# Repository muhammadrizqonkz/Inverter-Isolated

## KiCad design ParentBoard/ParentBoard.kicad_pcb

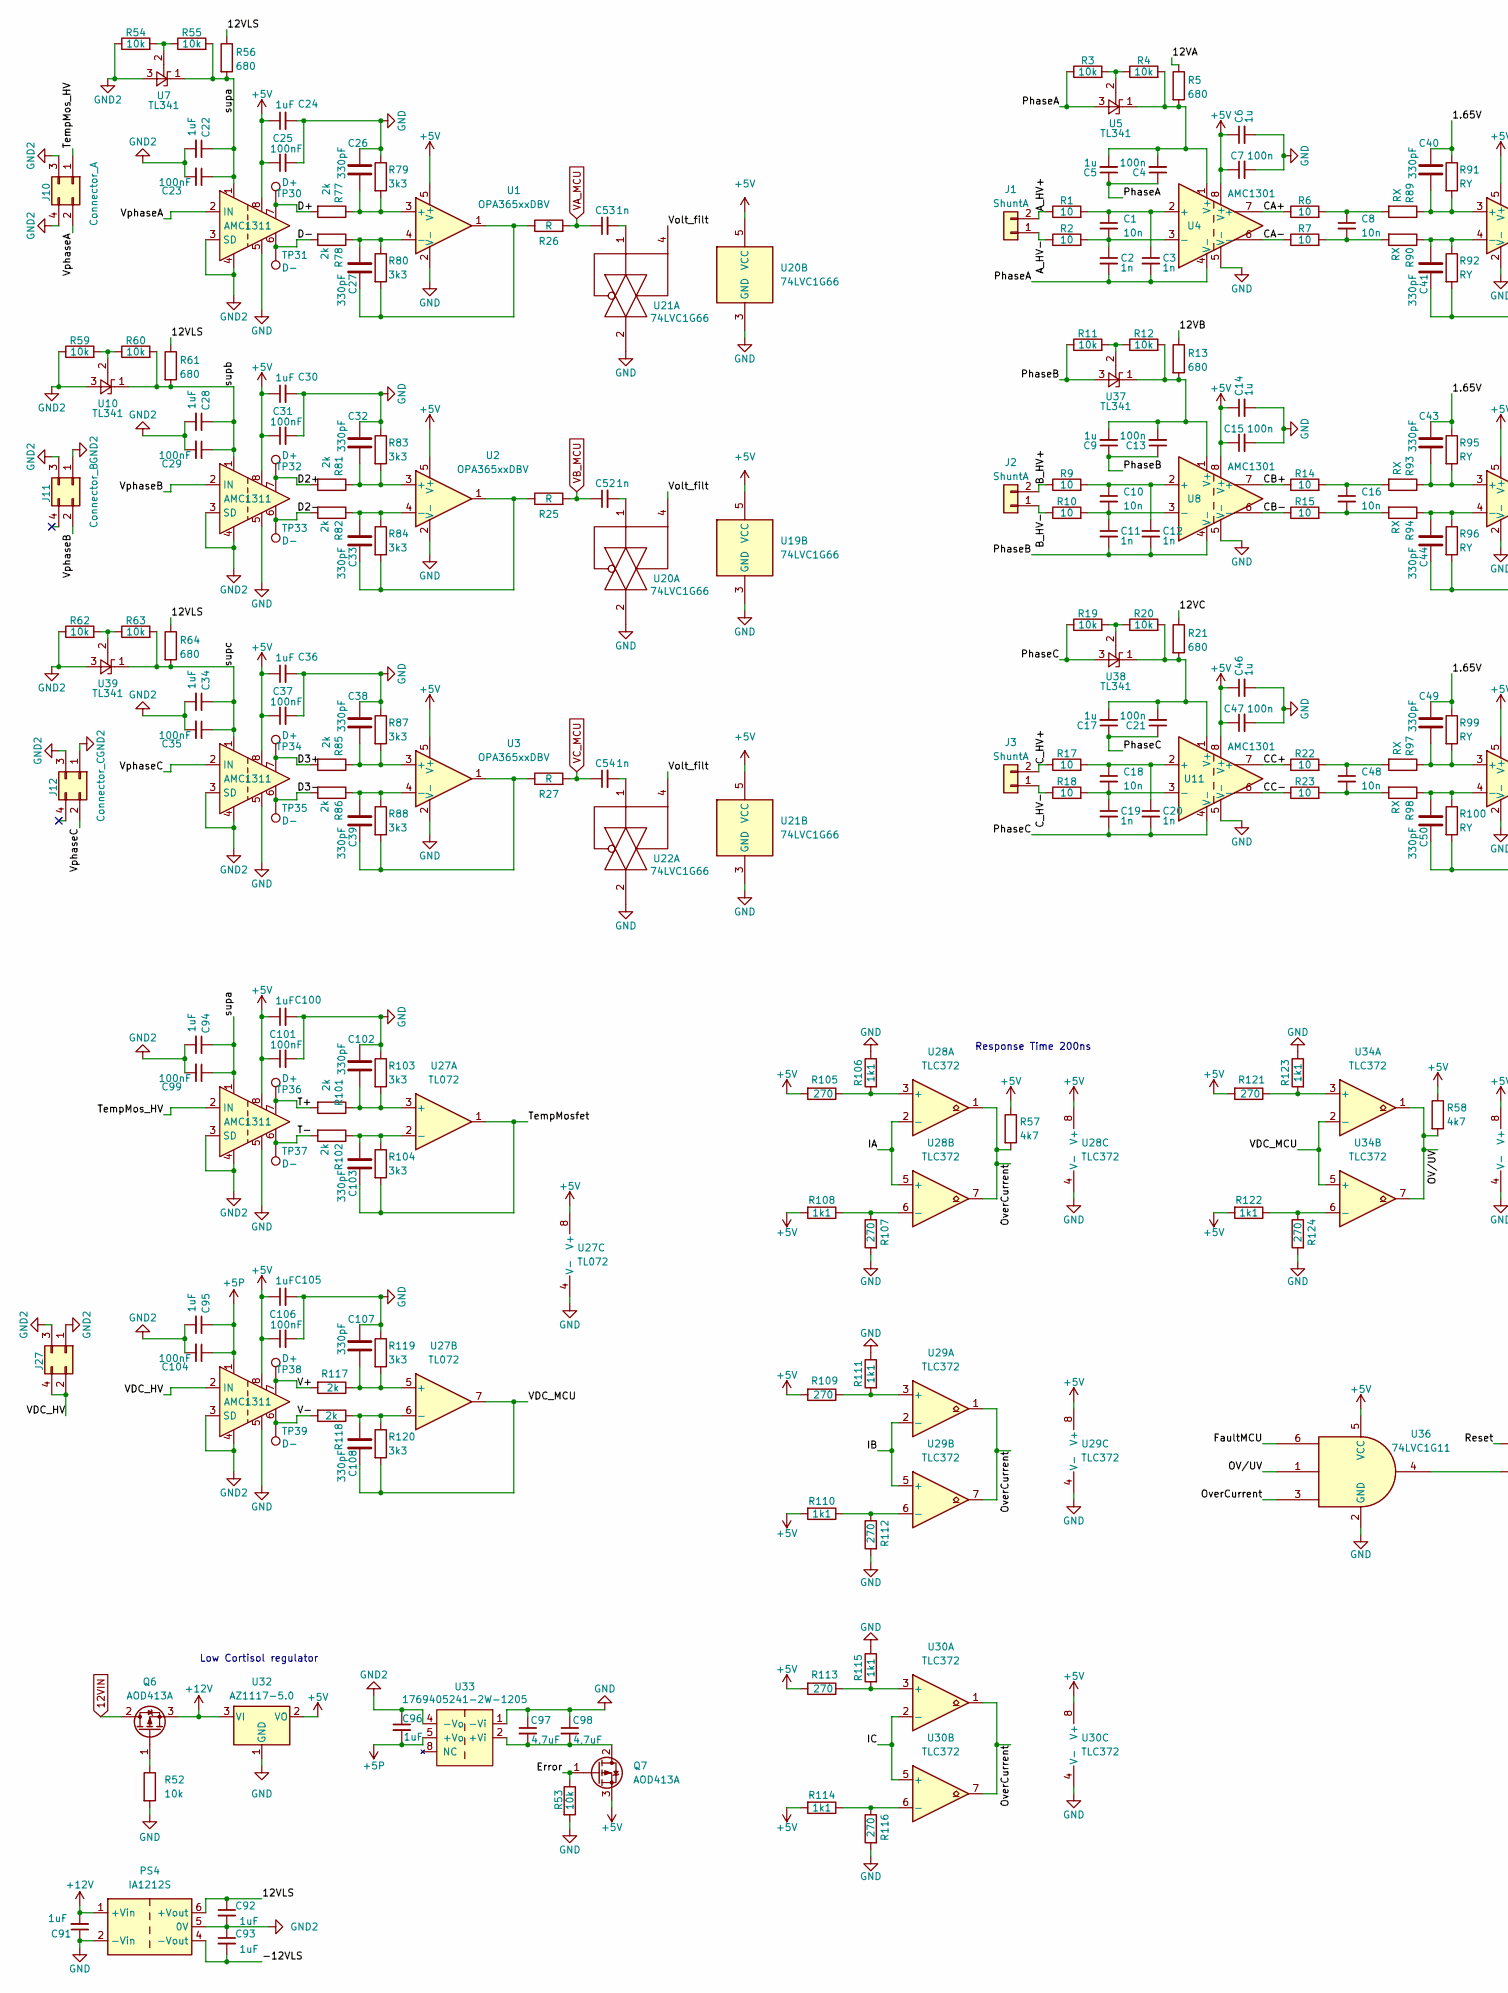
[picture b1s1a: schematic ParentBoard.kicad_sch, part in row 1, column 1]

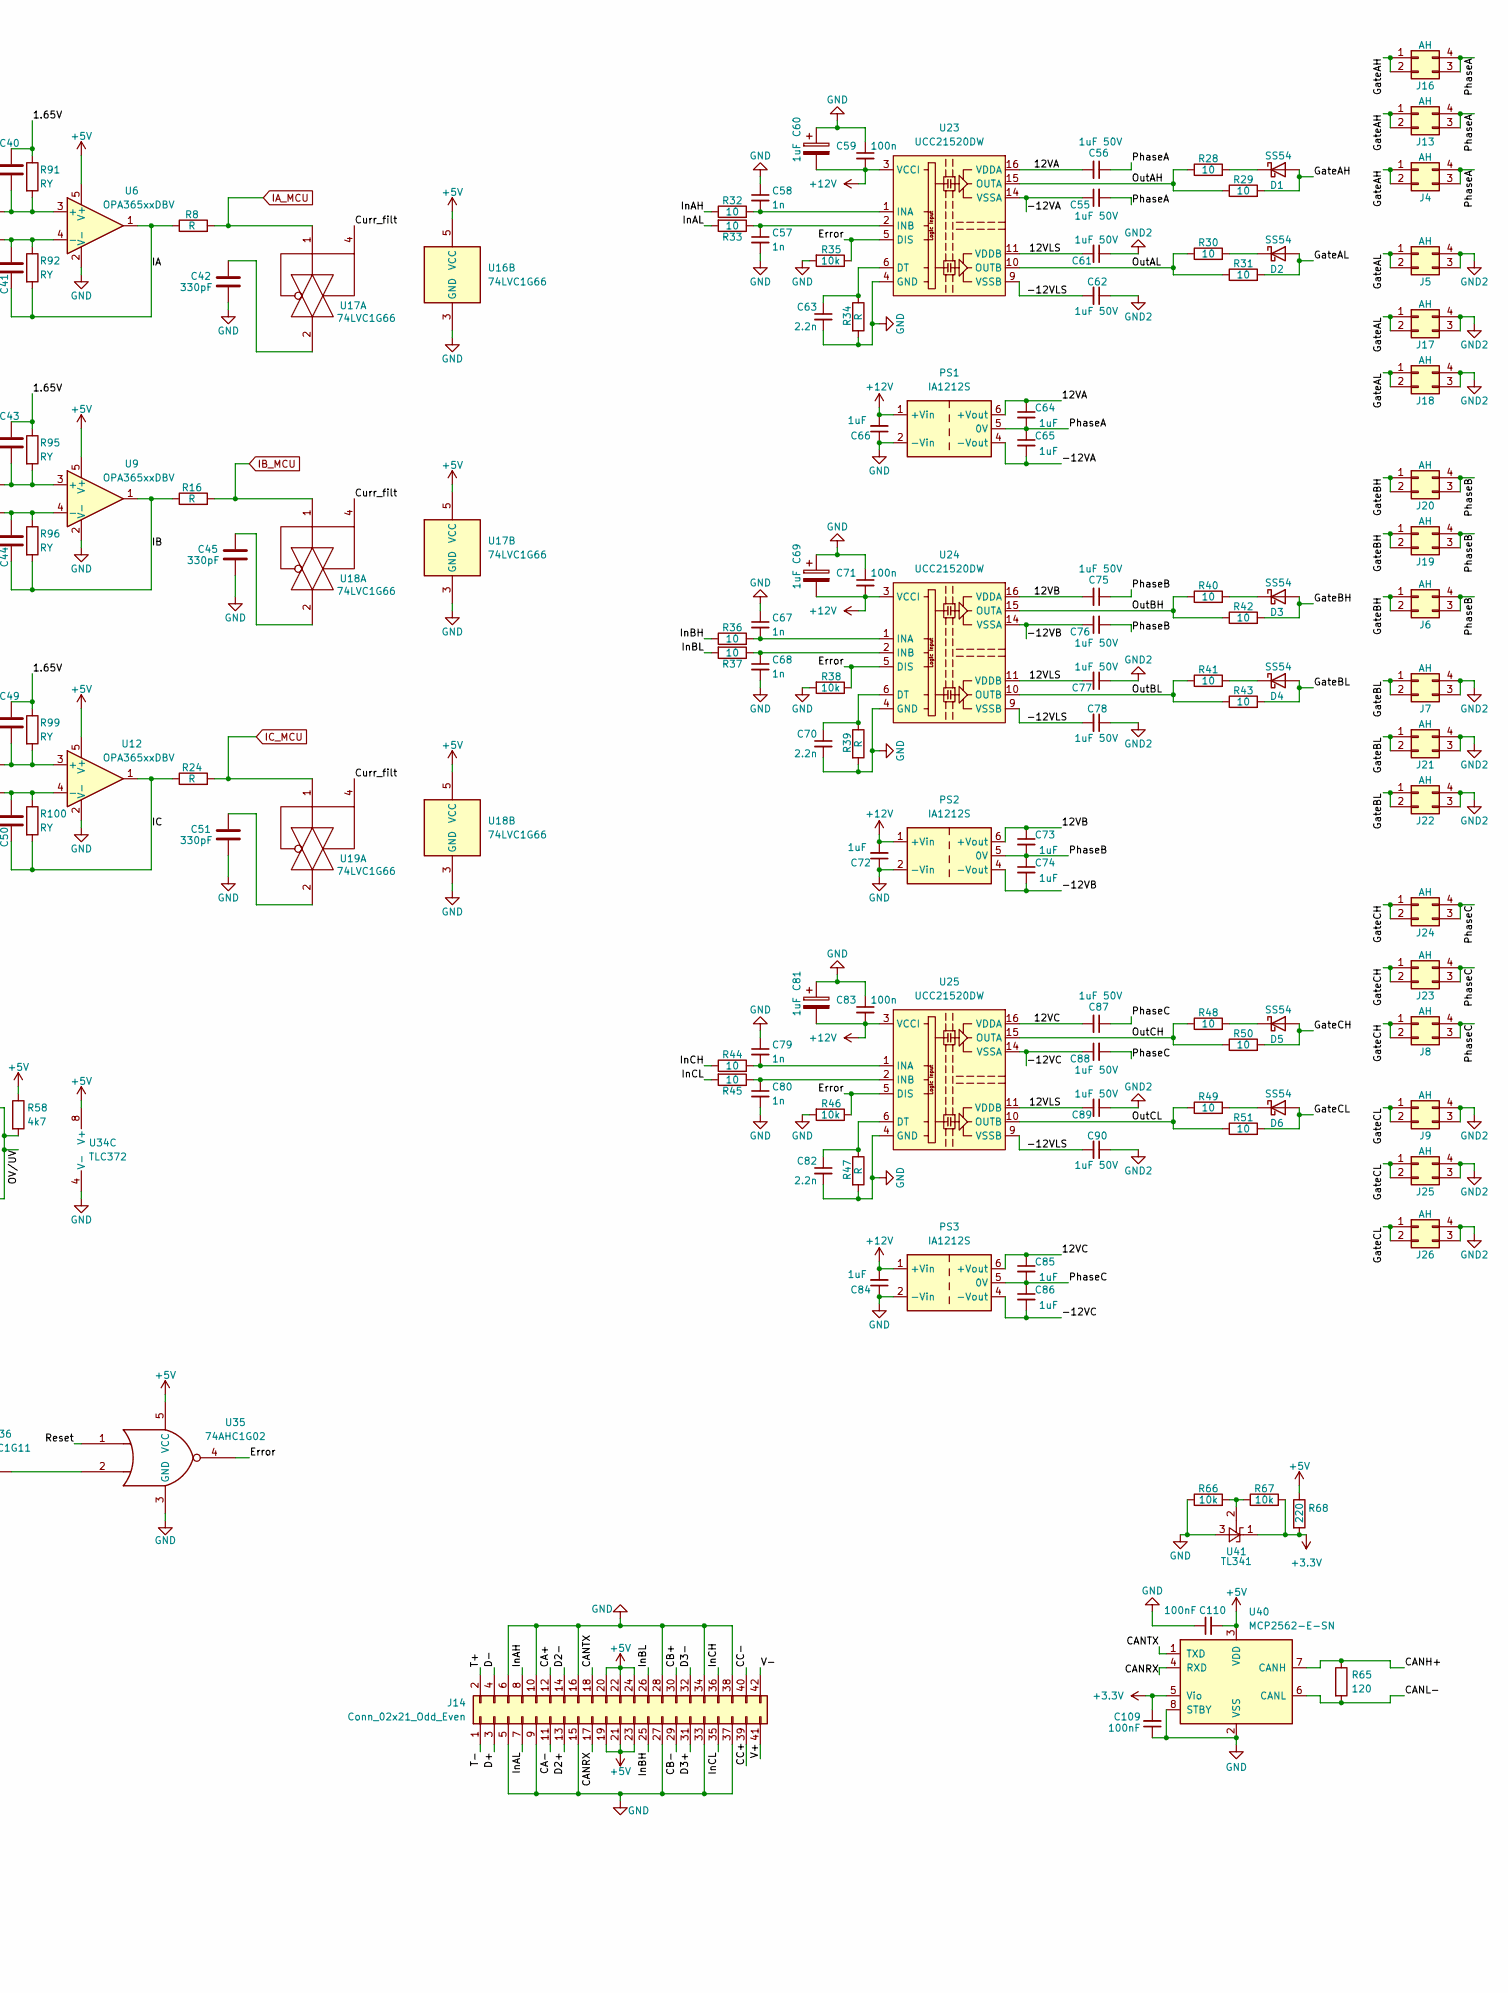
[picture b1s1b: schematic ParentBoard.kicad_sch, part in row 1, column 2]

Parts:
C1, C10, C18: 10n; C_0603_1608Metric_Pad1.08x0.95mm_HandSolder
C2, C3, C11, C12, C19, C20: 1n; C_0603_1608Metric_Pad1.08x0.95mm_HandSolder
C4, C7, C13, C15, C21, C47, C59, C71, C83: 100n; C_0805_2012Metric_Pad1.18x1.45mm_HandSolder
C5, C6, C9, C14, C17, C46: 1u; C_1206_3216Metric_Pad1.33x1.80mm_HandSolder
C8, C16, C48: 10n; C_0805_2012Metric_Pad1.18x1.45mm_HandSolder
C22, C24, C28, C30, C34, C36, C94, C95, C96, C100, C105: 1uF; C_0805_2012Metric_Pad1.18x1.45mm_HandSolder
C23, C25, C29, C31, C35, C37, C99, C101, C104, C106: 100nF; C_0805_2012Metric_Pad1.18x1.45mm_HandSolder
C26, C27, C32, C33, C38, C39, C40, C41, C42, C43, C44, C45, C49, C50, C51, C102, C103, C107, C108: 330pF; C_0805_2012Metric_Pad1.18x1.45mm_HandSolder
C52, C53, C54, C57, C58, C67, C68, C79, C80: 1n; C_0805_2012Metric_Pad1.18x1.45mm_HandSolder
C55, C56, C61, C62, C75, C76, C77, C78, C87, C88, C89, C90: 1uF 50V; C_1206_3216Metric_Pad1.33x1.80mm_HandSolder
C60, C64, C65, C66, C69, C72, C73, C74, C81, C84, C85, C86, C91, C92, C93: 1uF; C_1206_3216Metric_Pad1.33x1.80mm_HandSolder
C63, C70, C82: 2.2n; C_0805_2012Metric_Pad1.18x1.45mm_HandSolder
C97, C98: 4,7uF; C_0805_2012Metric_Pad1.18x1.45mm_HandSolder
C109, C110: 100nF
D1, D2, D3, D4, D5, D6: SS54; D_1206_3216Metric_Pad1.42x1.75mm_HandSolder
J1, J2, J3: ShuntA; PinHeader_1x02_P2.54mm_Vertical_SMD_Pin1Right
J4, J5, J6, J7, J8, J9, J13, J16, J17, J18, J19, J20, J21, J22, J23, J24, J25, J26: AH; PinHeader_2x02_P2.54mm_Vertical
J10: Connector_A; PinHeader_2x02_P2.54mm_Vertical
J11, J27: Connector_B; PinHeader_2x02_P2.54mm_Vertical
J12: Connector_C; PinHeader_2x02_P2.54mm_Vertical
J14: Conn_02x21_Odd_Even; PinHeader_2x21_P2.54mm_Vertical
PS1, PS2, PS3, PS4: IA1212S; Converter_DCDC_XP_POWER-IAxxxxS_THT
Q6, Q7: AOD413A; TO-252-2
R1, R2, R9, R10, R17, R18: 10; R_0603_1608Metric_Pad0.98x0.95mm_HandSolder
R3, R4, R11, R12, R19, R20, R54, R55, R59, R60, R62, R63: 10k; R_0402_1005Metric_Pad0.72x0.64mm_HandSolder
R5, R13, R21, R56, R61, R64: 680; R_0805_2012Metric_Pad1.20x1.40mm_HandSolder
R6, R7, R14, R15, R22, R23, R32, R33, R36, R37, R44, R45: 10; R_0805_2012Metric_Pad1.20x1.40mm_HandSolder
R8, R16, R24, R25, R26, R27, R34, R39, R47: R; R_0805_2012Metric_Pad1.20x1.40mm_HandSolder
R28, R29, R30, R31, R40, R41, R42, R43, R48, R49, R50, R51: 10; R_1206_3216Metric_Pad1.30x1.75mm_HandSolder
R35, R38, R46: 10k; R_0805_2012Metric_Pad1.20x1.40mm_HandSolder
R52, R53: 10k; R_0603_1608Metric_Pad0.98x0.95mm_HandSolder
R57, R58: 4k7; R_0805_2012Metric_Pad1.20x1.40mm_HandSolder
R65: 120; R_0805_2012Metric_Pad1.20x1.40mm_HandSolder
R66, R67: 10k; R_0805_2012Metric
R68: 220; R_0805_2012Metric_Pad1.20x1.40mm_HandSolder
R77, R78, R81, R82, R85, R86, R101, R102, R117, R118: 2k; R_0805_2012Metric_Pad1.20x1.40mm_HandSolder
R79, R80, R83, R84, R87, R88, R103, R104, R119, R120: 3k3; R_0805_2012Metric_Pad1.20x1.40mm_HandSolder
R89, R90, R93, R94, R97, R98: RX; R_0805_2012Metric_Pad1.20x1.40mm_HandSolder
R91, R92, R95, R96, R99, R100: RY; R_0805_2012Metric_Pad1.20x1.40mm_HandSolder
R105, R107, R109, R112, R113, R116, R121, R124: 270; R_0805_2012Metric_Pad1.20x1.40mm_HandSolder
R106, R108, R110, R111, R114, R115, R122, R123: 1k1; R_0805_2012Metric_Pad1.20x1.40mm_HandSolder
TP30, TP32, TP34, TP36, TP38: D+; TestPoint_Pad_D1.0mm
TP31, TP33, TP35, TP37, TP39: D-; TestPoint_Pad_D1.0mm
U1, U2, U3, U6, U9, U12: OPA365xxDBV; SOT-23-5
U4, U8, U11: AMC1301; SOIC-8_7.5x5.85mm_P1.27mm
U5, U7, U10, U37, U38, U39, U41: TL341; SOT-23-3
U13, U14, U15, U26, U31: AMC1311; SOIC-8_7.5x5.85mm_P1.27mm
U16, U17, U18, U19, U20, U21, U22: 74LVC1G66; SOT-23-5
U23, U24, U25: UCC21520DW; SOIC-16W_7.5x10.3mm_P1.27mm
U27: TL072; SOIC-8_3.9x4.9mm_P1.27mm
U28, U29, U30, U34: TLC372; SOIC-8_3.9x4.9mm_P1.27mm
U32: AZ1117-5.0; TO-252-2
U33: 1769405241-2W-1205; Wurth_0505
U35: 74AHC1G02; SOT-23-5_HandSoldering
U36: 74LVC1G11; TSOT-23-6_HandSoldering
U40: MCP2562-E-SN; SOIC-8_3.9x4.9mm_P1.27mm

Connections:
12VIN: Q6.2 (D)
+3.3V: C109.2, R67.2, R68.2, U40.5 (Vio), U41.1 (K)
+5P: C95.1, C96.2, C104.1, U31.1, U33.5 (+Vo)
+5V: C6.1, C7.1, C14.1, C15.1, C24.1, C25.1, C30.1, C31.1, C36.1, C37.1, C46.1, C47.1, C100.1, C101.1, C105.1, C106.1, C110.2, J14.19, J14.20, J14.21, J14.22, J14.23, J14.24, Q7.3 (S), R57.1, R58.1, R68.1, R105.2, R108.2, R109.2, R110.2, R113.2, R114.2, R121.2, R122.2, U1.5 (V+), U2.5 (V+), U3.5 (V+), U4.8 (V+), U6.5 (V+), U8.8 (V+), U9.5 (V+), U11.8 (V+), U12.5 (V+), U13.8, U14.8, U15.8, U16.5 (VCC), U17.5 (VCC), U18.5 (VCC), U19.5 (VCC), U20.5 (VCC), U21.5 (VCC), U26.8, U27.8 (V+), U28.8 (V+), U29.8 (V+), U30.8 (V+), U31.8, U32.2 (VO), U34.8 (V+), U35.5 (VCC), U36.5 (VCC), U40.3 (VDD)
+12V: C59.2, C60.2, C66.2, C69.2, C71.2, C72.2, C81.2, C83.2, C84.2, C91.2, PS1.1 (+Vin), PS2.1 (+Vin), PS3.1 (+Vin), PS4.1 (+Vin), Q6.3 (S), U23.3 (VCCI), U23.8 (VCCI), U24.3 (VCCI), U24.8 (VCCI), U25.3 (VCCI), U25.8 (VCCI), U32.3 (VI)
/1.65V: C40.1, C43.1, C49.1, R91.1, R95.1, R99.1
/12VA: C56.2, C64.1, PS1.6 (+Vout), R5.1, U23.16 (VDDA)
/12VB: C73.1, C75.2, PS2.6 (+Vout), R13.1, U24.16 (VDDA)
/12VC: C85.1, C87.2, PS3.6 (+Vout), R21.1, U25.16 (VDDA)
/12VLS: C61.2, C77.2, C89.2, C92.1, PS4.6 (+Vout), R56.1, R61.1, R64.1, U23.11 (VDDB), U24.11 (VDDB), U25.11 (VDDB)
/-12VA: C55.1, C65.2, PS1.4 (-Vout), U23.14 (VSSA)
/-12VB: C74.2, C76.1, PS2.4 (-Vout), U24.14 (VSSA)
/-12VC: C86.2, C88.1, PS3.4 (-Vout), U25.14 (VSSA)
/-12VLS: C62.2, C78.2, C90.2, C93.2, PS4.4 (-Vout), U23.9 (VSSB), U24.9 (VSSB), U25.9 (VSSB)
/A_HV+: J1.2, R1.1
/A_HV-: J1.1, R2.1
/B_HV+: J2.2, R9.1
/B_HV-: J2.1, R10.1
/CA+: J14.12, R6.1, U4.7 (+)
/CA-: J14.11, R7.1, U4.6 (-)
/CANH: R65.1, U40.7 (CANH)
/CANL: R65.2, U40.6 (CANL)
/CANRX: J14.17, U40.4 (RXD)
/CANTX: J14.18, U40.1 (TXD)
/CB+: J14.30, R14.1, U8.7 (+)
/CB-: J14.29, R15.1, U8.6 (-)
/CC+: J14.39, R22.1, U11.7 (+)
/CC-: J14.40, R23.1, U11.6 (-)
/C_HV+: J3.2, R17.1
/C_HV-: J3.1, R18.1
/Curr_filt: U17.4, U18.4, U19.4
/D2+: J14.13, R81.2, TP32.1 (1_1), U14.7
/D2-: J14.14, R82.2, TP33.1 (1_1), U14.6
/D3+: J14.31, R85.2, TP34.1 (1_1), U15.7
/D3-: J14.32, R86.2, TP35.1 (1_1), U15.6
/D+: J14.3, R77.2, TP30.1 (1_1), U13.7
/D-: J14.4, R78.2, TP31.1 (1_1), U13.6
/Error: Q7.1 (G), R35.1, R38.1, R46.1, R53.1, U23.5 (DIS), U24.5 (DIS), U25.5 (DIS), U35.4
/FaultMCU: U36.6
/GateAH: D1.2 (A), J4.1, J4.2, J13.1, J13.2, J16.1, J16.2, R29.2
/GateAL: D2.2 (A), J5.1, J5.2, J17.1, J17.2, J18.1, J18.2, R31.2
/GateBH: D3.2 (A), J6.1, J6.2, J19.1, J19.2, J20.1, J20.2, R42.2
/GateBL: D4.2 (A), J7.1, J7.2, J21.1, J21.2, J22.1, J22.2, R43.2
/GateCH: D5.2 (A), J8.1, J8.2, J23.1, J23.2, J24.1, J24.2, R50.2
/GateCL: D6.2 (A), J9.1, J9.2, J25.1, J25.2, J26.1, J26.2, R51.2
/IA: C41.1, R8.1, R92.2, U6.1, U28.2 (-), U28.5 (+)
/IB: C44.1, R16.1, R96.2, U9.1, U29.2 (-), U29.5 (+)
/IC: C50.1, R24.1, R100.2, U12.1, U30.2 (-), U30.5 (+)
/InAH: J14.8, R32.1
/InAL: J14.7, R33.2
/InBH: J14.25, R36.1
/InBL: J14.26, R37.2
/InCH: J14.36, R44.1
/InCL: J14.35, R45.2
/OV/UV: R58.2, U34.1, U34.7, U36.1
/OutAH: R28.1, R29.1, U23.15 (OUTA)
/OutAL: R30.1, R31.1, U23.10 (OUTB)
/OutBH: R40.1, R42.1, U24.15 (OUTA)
/OutBL: R41.1, R43.1, U24.10 (OUTB)
/OutCH: R48.1, R50.1, U25.15 (OUTA)
/OutCL: R49.1, R51.1, U25.10 (OUTB)
/OverCurrent: R57.2, U28.1, U28.7, U29.1, U29.7, U30.1, U30.7, U36.3
/PhaseA: C2.2, C3.2, C4.1, C5.1, C55.2, C56.1, C64.2, C65.1, J4.3, J4.4, J13.3, J13.4, J16.3, J16.4, PS1.5 (0V), R3.1, U4.4 (V-), U5.3 (A)
/PhaseB: C9.1, C11.2, C12.2, C13.1, C73.2, C74.1, C75.1, C76.2, J6.3, J6.4, J19.3, J19.4, J20.3, J20.4, PS2.5 (0V), R11.1, U8.4 (V-), U37.3 (A)
/PhaseC: C17.1, C19.2, C20.2, C21.1, C85.2, C86.1, C87.1, C88.2, J8.3, J8.4, J23.3, J23.4, J24.3, J24.4, PS3.5 (0V), R19.1, U11.4 (V-), U38.3 (A)
/Reset: U35.1
/T+: J14.2, R101.2, TP36.1 (1_1), U26.7
/T-: J14.1, R102.2, TP37.1 (1_1), U26.6
/TempMos_HV: J10.1, U26.2 (IN)
/TempMosfet: C103.1, R104.2, U27.1
/V+: J14.41, R117.2, TP38.1 (1_1), U31.7
/V-: J14.42, R118.2, TP39.1 (1_1), U31.6
/VDC_HV: J27.2, J27.4, U31.2 (IN)
/VDC_MCU: C108.1, R120.2, U27.7, U34.2 (-), U34.5 (+)
/Volt_filt: U20.4, U21.4, U22.4
/VphaseA: J10.2, U13.2 (IN)
/VphaseB: J11.2, U14.2 (IN)
/VphaseC: J12.2, U15.2 (IN)
/supa: C22.1, C23.1, C94.1, C99.1, R55.2, R56.2, U7.1 (K), U13.1, U26.1
/supb: C28.1, C29.1, R60.2, R61.2, U10.1 (K), U14.1
/supc: C34.1, C35.1, R63.2, R64.2, U15.1, U39.1 (K)
GND: C6.2, C7.2, C14.2, C15.2, C24.2, C25.2, C26.1, C30.2, C31.2, C32.1, C36.2, C37.2, C38.1, C42.1, C45.1, C46.2, C47.2, C51.1, C57.2, C58.1, C59.1, C60.1, C63.2, C66.1, C67.1, C68.2, C69.1, C70.2, C71.1, C72.1, C79.1, C80.2, C81.1, C82.2, C83.1, C84.1, C91.1, C97.1, C98.1, C100.2, C101.2, C102.1, C105.2, C106.2, C107.1, C109.1, C110.1, J14.5, J14.6, J14.9, J14.10, J14.15, J14.16, J14.27, J14.28, J14.33, J14.34, J14.37, J14.38, PS1.2 (-Vin), PS2.2 (-Vin), PS3.2 (-Vin), PS4.2 (-Vin), R34.2, R35.2, R38.2, R39.2, R46.2, R47.2, R52.2, R53.2, R66.1, R79.1, R83.1, R87.1, R103.1, R106.1, R107.2, R111.1, R112.2, R115.1, R116.2, R119.1, R123.1, R124.2, U1.2 (V-), U2.2 (V-), U3.2 (V-), U4.5 (V-), U6.2 (V-), U8.5 (V-), U9.2 (V-), U11.5 (V-), U12.2 (V-), U13.5, U14.5, U15.5, U16.3 (GND), U17.3 (GND), U18.3 (GND), U19.3 (GND), U20.2, U20.3 (GND), U21.2, U21.3 (GND), U22.2, U23.4 (GND), U24.4 (GND), U25.4 (GND), U26.5, U27.4 (V-), U28.4 (V-), U29.4 (V-), U30.4 (V-), U31.5, U32.1 (GND), U33.1 (-Vi), U34.4 (V-), U35.3 (GND), U36.2 (GND), U40.2 (VSS), U40.8 (STBY), U41.3 (A)
GND2: C22.2, C23.2, C28.2, C29.2, C34.2, C35.2, C61.1, C62.1, C77.1, C78.1, C89.1, C90.1, C92.2, C93.1, C94.2, C95.2, C96.1, C99.2, C104.2, J5.3, J5.4, J7.3, J7.4, J9.3, J9.4, J10.3, J10.4, J11.1, J11.3, J12.1, J12.3, J17.3, J17.4, J18.3, J18.4, J21.3, J21.4, J22.3, J22.4, J25.3, J25.4, J26.3, J26.4, J27.1, J27.3, PS4.5 (0V), R54.1, R59.1, R62.1, U7.3 (A), U10.3 (A), U13.3 (SD), U13.4, U14.3 (SD), U14.4, U15.3 (SD), U15.4, U26.3 (SD), U26.4, U31.3 (SD), U31.4, U33.4 (-Vo), U39.3 (A)
IA_MCU: R8.2, U17.1
IB_MCU: R16.2, U18.1
IC_MCU: R24.2, U19.1
unnamed: C1.1, C3.1, R1.2, U4.2 (+)
unnamed: C1.2, C2.1, R2.2, U4.3 (-)
unnamed: C8.1, R6.2, R89.2
unnamed: C8.2, R7.2, R90.2
unnamed: C10.1, C12.1, R9.2, U8.2 (+)
unnamed: C10.2, C11.1, R10.2, U8.3 (-)
unnamed: C16.1, R14.2, R93.2
unnamed: C16.2, R15.2, R94.2
unnamed: C18.1, C20.1, R17.2, U11.2 (+)
unnamed: C18.2, C19.1, R18.2, U11.3 (-)
unnamed: C27.1, R26.1, R80.2, U1.1
unnamed: C33.1, R25.1, R84.2, U2.1
unnamed: C39.1, R27.1, R88.2, U3.1
unnamed: C42.2, U17.2
unnamed: C45.2, U18.2
unnamed: C48.1, R22.2, R97.2
unnamed: C48.2, R23.2, R98.2
unnamed: C51.2, U19.2
unnamed: C52.2, U20.1
unnamed: C53.2, U21.1
unnamed: C54.2, U22.1
unnamed: D1.1 (K), R28.2
unnamed: D2.1 (K), R30.2
unnamed: D3.1 (K), R40.2
unnamed: D4.1 (K), R41.2
unnamed: D5.1 (K), R48.2
unnamed: D6.1 (K), R49.2
unnamed: Q6.1 (G), R52.1
unnamed: C97.2, C98.2, Q7.2 (D), U33.2 (+Vi)
unnamed: C26.2, R77.1, R79.2, U1.3 (+)
unnamed: C27.2, R78.1, R80.1, U1.4 (-)
unnamed: C32.2, R81.1, R83.2, U2.3 (+)
unnamed: C33.2, R82.1, R84.1, U2.4 (-)
unnamed: C38.2, R85.1, R87.2, U3.3 (+)
unnamed: C39.2, R86.1, R88.1, U3.4 (-)
unnamed: C4.2, C5.2, R4.2, R5.2, U4.1 (V+), U5.1 (K)
unnamed: R3.2, R4.1, U5.2 (REF)
unnamed: C40.2, R89.1, R91.2, U6.3 (+)
unnamed: C41.2, R90.1, R92.1, U6.4 (-)
unnamed: R54.2, R55.1, U7.2 (REF)
unnamed: C43.2, R93.1, R95.2, U9.3 (+)
unnamed: C44.2, R94.1, R96.1, U9.4 (-)
unnamed: R59.2, R60.1, U10.2 (REF)
unnamed: C49.2, R97.1, R99.2, U12.3 (+)
unnamed: C50.2, R98.1, R100.1, U12.4 (-)
unnamed: C63.1, R34.1, U23.6 (DT)
unnamed: C58.2, R32.2, U23.1 (INA)
unnamed: C57.1, R33.1, U23.2 (INB)
unnamed: C70.1, R39.1, U24.6 (DT)
unnamed: C67.2, R36.2, U24.1 (INA)
unnamed: C68.1, R37.1, U24.2 (INB)
unnamed: C82.1, R47.1, U25.6 (DT)
unnamed: C79.2, R44.2, U25.1 (INA)
unnamed: C80.1, R45.1, U25.2 (INB)
unnamed: C102.2, R101.1, R103.2, U27.3 (+)
unnamed: C103.2, R102.1, R104.1, U27.2 (-)
unnamed: C107.2, R117.1, R119.2, U27.5 (+)
unnamed: C108.2, R118.1, R120.1, U27.6 (-)
unnamed: R105.1, R106.2, U28.3 (+)
unnamed: R107.1, R108.1, U28.6 (-)
unnamed: R109.1, R111.2, U29.3 (+)
unnamed: R110.1, R112.1, U29.6 (-)
unnamed: R113.1, R115.2, U30.3 (+)
unnamed: R114.1, R116.1, U30.6 (-)
unnamed: R121.1, R123.2, U34.3 (+)
unnamed: R122.1, R124.1, U34.6 (-)
unnamed: U35.2, U36.4
unnamed: C9.2, C13.2, R12.2, R13.2, U8.1 (V+), U37.1 (K)
unnamed: R11.2, R12.1, U37.2 (REF)
unnamed: C17.2, C21.2, R20.2, R21.2, U11.1 (V+), U38.1 (K)
unnamed: R19.2, R20.1, U38.2 (REF)
unnamed: R62.2, R63.1, U39.2 (REF)
unnamed: R66.2, R67.1, U41.2 (REF)
VA_MCU: C53.1, R26.2
VB_MCU: C52.1, R25.2
VC_MCU: C54.1, R27.2

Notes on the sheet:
Low Cortisol regulator
Response Time 200ns

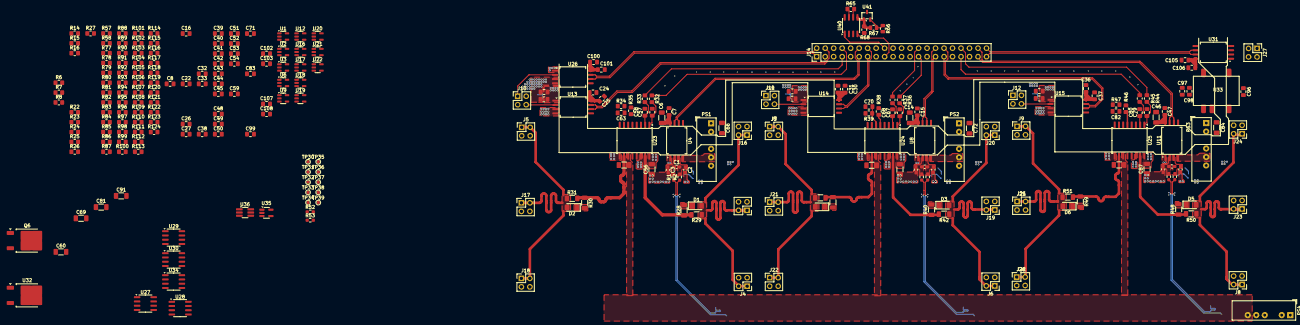
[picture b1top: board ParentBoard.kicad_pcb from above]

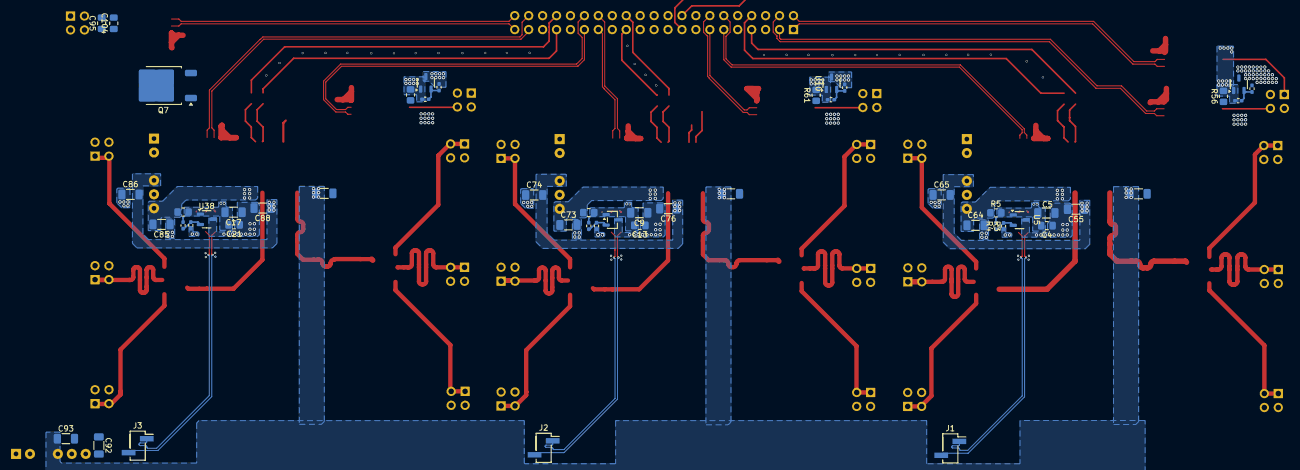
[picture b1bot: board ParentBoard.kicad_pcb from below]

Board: 4 copper layers, 313 parts (50 on the bottom side), 159 nets.

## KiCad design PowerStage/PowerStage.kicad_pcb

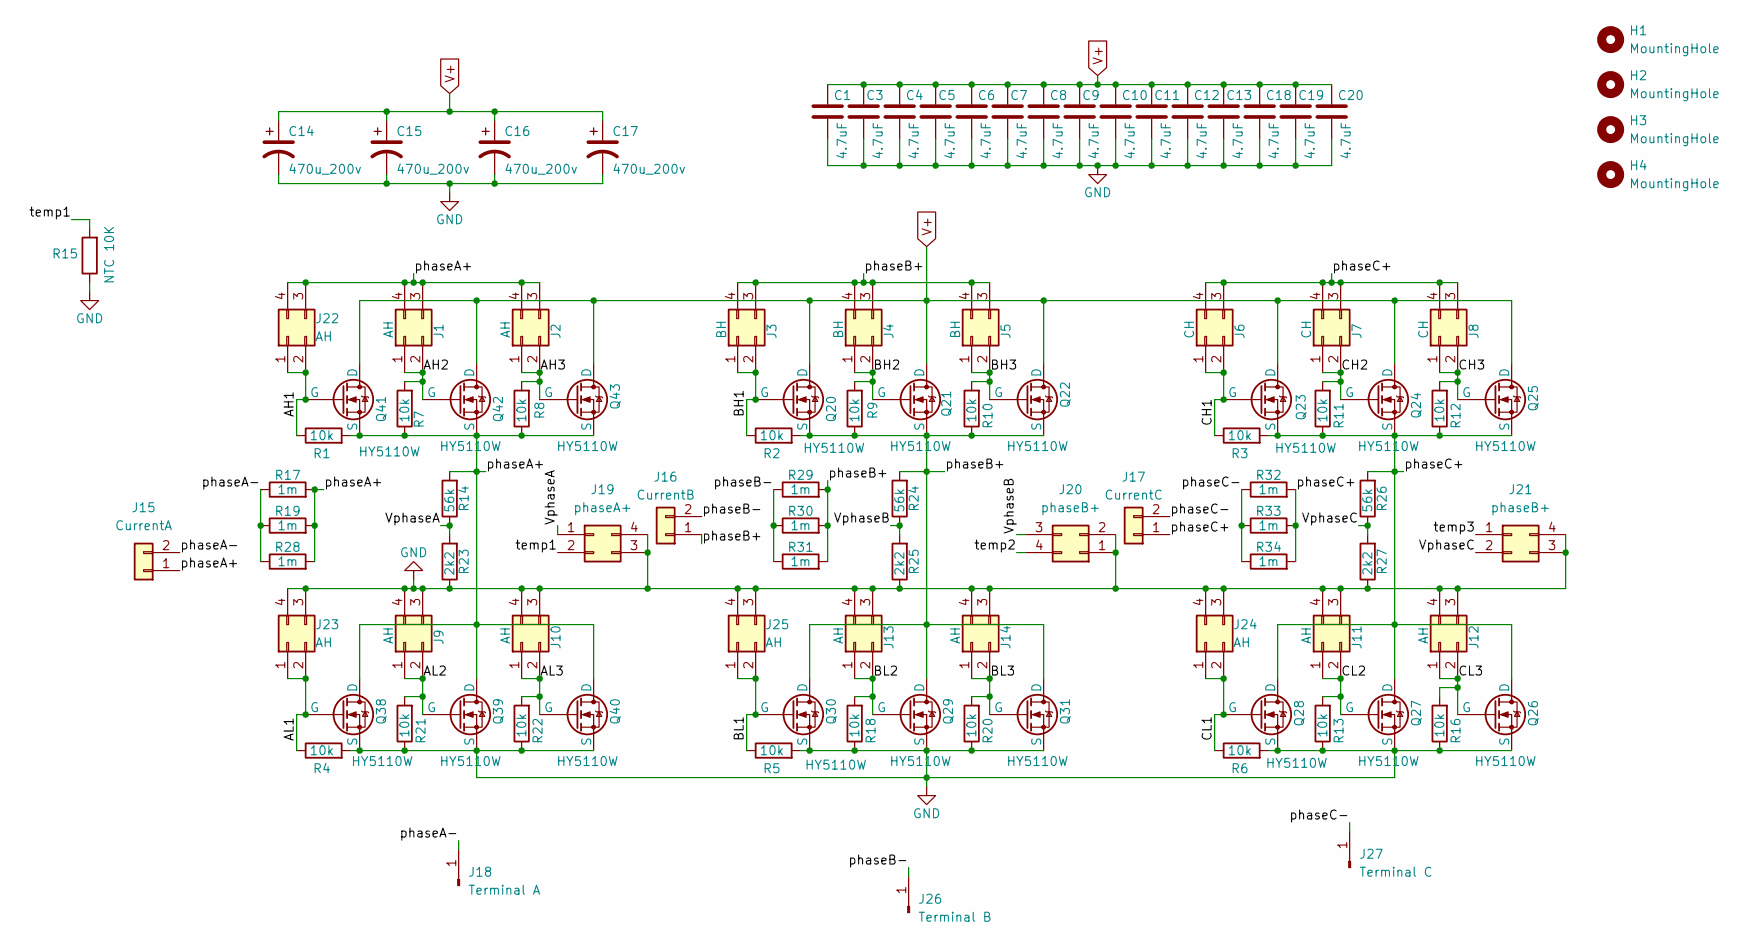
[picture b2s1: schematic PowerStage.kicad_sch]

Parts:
C1, C3, C4, C5, C6, C7, C8, C9, C10, C11, C12, C13, C18, C19, C20: 4.7uF; C_3640_9110Metric_Pad2.10x10.45mm_HandSolder
C14, C15, C16, C17: 470u_200v; CP_Radial_D25.0mm_P10.00mm_SnapIn
H1, H2, H3, H4: MountingHole; MountingHole_3mm_Pad_Via
J1, J2, J9, J10, J11, J12, J13, J14, J22, J23, J24, J25: AH; pinheader_2.54_sangar
J3, J4, J5: BH; pinheader_2.54_sangar
J6, J7, J8: CH; pinheader_2.54_sangar
J15: CurrentA; PinSocket_1x02_P2.54mm_Vertical_SMD_Pin1Left
J16: CurrentB; PinSocket_1x02_P2.54mm_Vertical_SMD_Pin1Left
J17: CurrentC; PinSocket_1x02_P2.54mm_Vertical_SMD_Pin1Left
J18: Terminal A; 225685-E
J19: phaseA+; PinHeader_2x02_P2.54mm_Vertical_SMD
J20, J21: phaseB+; PinHeader_2x02_P2.54mm_Vertical_SMD
J26: Terminal B; 225685-E
J27: Terminal C; 225685-E
Q20, Q21, Q22, Q23, Q24, Q25, Q26, Q27, Q28, Q29, Q30, Q31, Q38, Q39, Q40, Q41, Q42, Q43: HY5110W; TO-247 Horizontal Tabup
R1, R2, R3, R4, R5, R6, R7, R8, R9, R10, R11, R12, R13, R16, R18, R20, R21, R22: 10k; R_0805_2012Metric_Pad1.20x1.40mm_HandSolder
R14, R24, R26: 56k; R_0805_2012Metric_Pad1.20x1.40mm_HandSolder
R15: NTC 10K; R_Axial_DIN0204_L3.6mm_D1.6mm_P1.90mm_Vertical
R17, R19, R28, R29, R30, R31, R32, R33, R34: 1m; ShuntResistor_P2mmD10mm
R23, R25, R27: 2k2; R_0805_2012Metric_Pad1.20x1.40mm_HandSolder

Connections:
/AH1: J22.1, J22.2, Q41.2 (G), R1.1
/AH2: J1.1, J1.2, Q42.2 (G), R7.2
/AH3: J2.1, J2.2, Q43.2 (G), R8.2
/AL1: J23.1, J23.2, Q38.2 (G), R4.1
/AL2: J9.1, J9.2, Q39.2 (G), R21.2
/AL3: J10.1, J10.2, Q40.2 (G), R22.2
/BH1: J3.1, J3.2, Q20.2 (G), R2.1
/BH2: J4.1, J4.2, Q21.2 (G), R9.2
/BH3: J5.1, J5.2, Q22.2 (G), R10.2
/BL1: J25.1, J25.2, Q30.2 (G), R5.1
/BL2: J13.1, J13.2, Q29.2 (G), R18.2
/BL3: J14.1, J14.2, Q31.2 (G), R20.2
/CH1: J6.1, J6.2, Q23.2 (G), R3.1
/CH2: J7.1, J7.2, Q24.2 (G), R11.2
/CH3: J8.1, J8.2, Q25.2 (G), R12.2
/CL1: J24.1, J24.2, Q28.2 (G), R6.1
/CL2: J11.1, J11.2, Q27.2 (G), R13.2
/CL3: J12.1, J12.2, Q26.2 (G), R16.2
/VphaseA: J19.1, R14.1, R23.2
/VphaseB: J20.3, R24.1, R25.2
/VphaseC: J21.2, R26.1, R27.2
/phaseA+: J1.3, J1.4, J2.3, J2.4, J15.1, J22.3, J22.4, Q38.1 (D), Q39.1 (D), Q40.1 (D), Q41.3 (S), Q42.3 (S), Q43.3 (S), R1.2, R7.1, R8.1, R14.2, R17.2, R19.2, R28.2
/phaseA-: J15.2, J18.1 (Pin_1_1), R17.1, R19.1, R28.1
/phaseB+: J3.3, J3.4, J4.3, J4.4, J5.3, J5.4, J16.1, Q20.3 (S), Q21.3 (S), Q22.3 (S), Q29.1 (D), Q30.1 (D), Q31.1 (D), R2.2, R9.1, R10.1, R24.2, R29.2, R30.2, R31.2
/phaseB-: J16.2, J26.1 (Pin_1_1), R29.1, R30.1, R31.1
/phaseC+: J6.3, J6.4, J7.3, J7.4, J8.3, J8.4, J17.1, Q23.3 (S), Q24.3 (S), Q25.3 (S), Q26.1 (D), Q27.1 (D), Q28.1 (D), R3.2, R11.1, R12.1, R26.2, R32.2, R33.2, R34.2
/phaseC-: J17.2, J27.1 (Pin_1_1), R32.1, R33.1, R34.1
/temp1: J19.2, R15.2
/temp2: J20.4
/temp3: J21.1
GND: C1.2, C3.2, C4.2, C5.2, C6.2, C7.2, C8.2, C9.2, C10.2, C11.2, C12.2, C13.2, C14.2, C15.2, C16.2, C17.2, C18.2, C19.2, C20.2, J9.3, J9.4, J10.3, J10.4, J11.3, J11.4, J12.3, J12.4, J13.3, J13.4, J14.3, J14.4, J19.3, J19.4, J20.1, J20.2, J21.3, J21.4, J23.3, J23.4, J24.3, J24.4, J25.3, J25.4, Q26.3 (S), Q27.3 (S), Q28.3 (S), Q29.3 (S), Q30.3 (S), Q31.3 (S), Q38.3 (S), Q39.3 (S), Q40.3 (S), R4.2, R5.2, R6.2, R13.1, R15.1, R16.1, R18.1, R20.1, R21.1, R22.1, R23.1, R25.1, R27.1
V+: C1.1, C3.1, C4.1, C5.1, C6.1, C7.1, C8.1, C9.1, C10.1, C11.1, C12.1, C13.1, C14.1, C15.1, C16.1, C17.1, C18.1, C19.1, C20.1, Q20.1 (D), Q21.1 (D), Q22.1 (D), Q23.1 (D), Q24.1 (D), Q25.1 (D), Q41.1 (D), Q42.1 (D), Q43.1 (D)

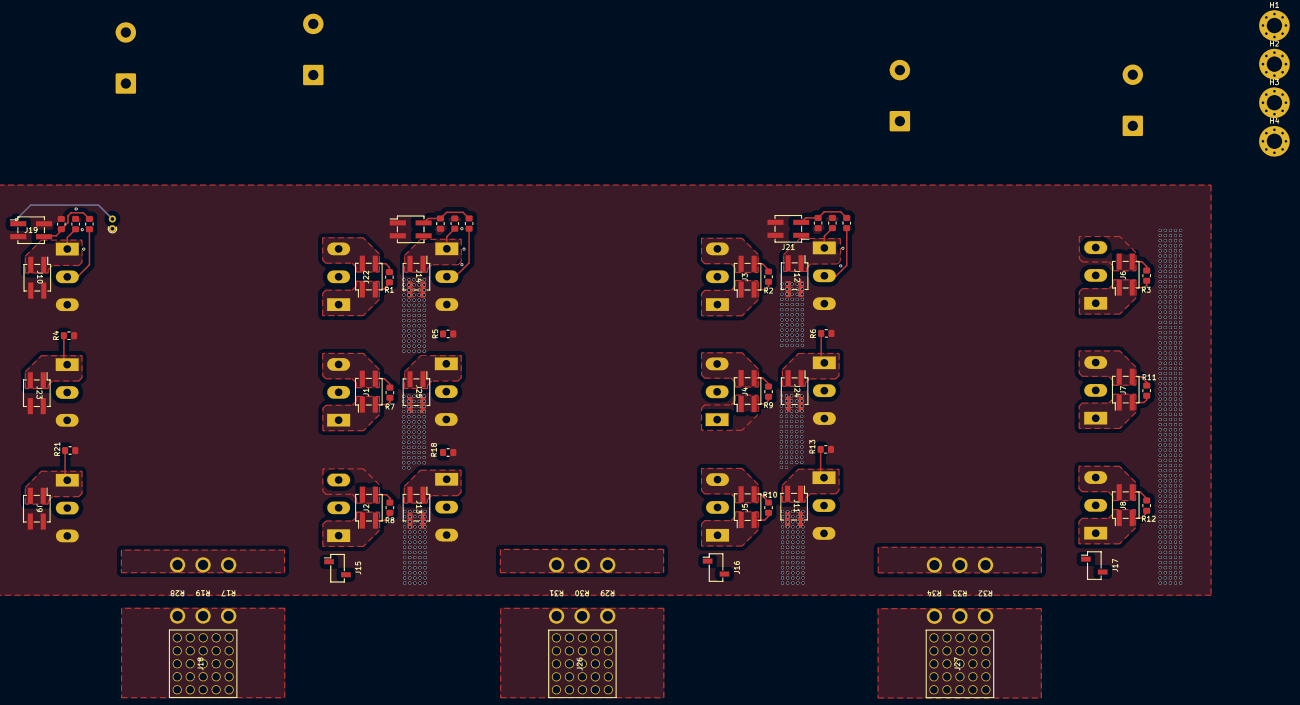
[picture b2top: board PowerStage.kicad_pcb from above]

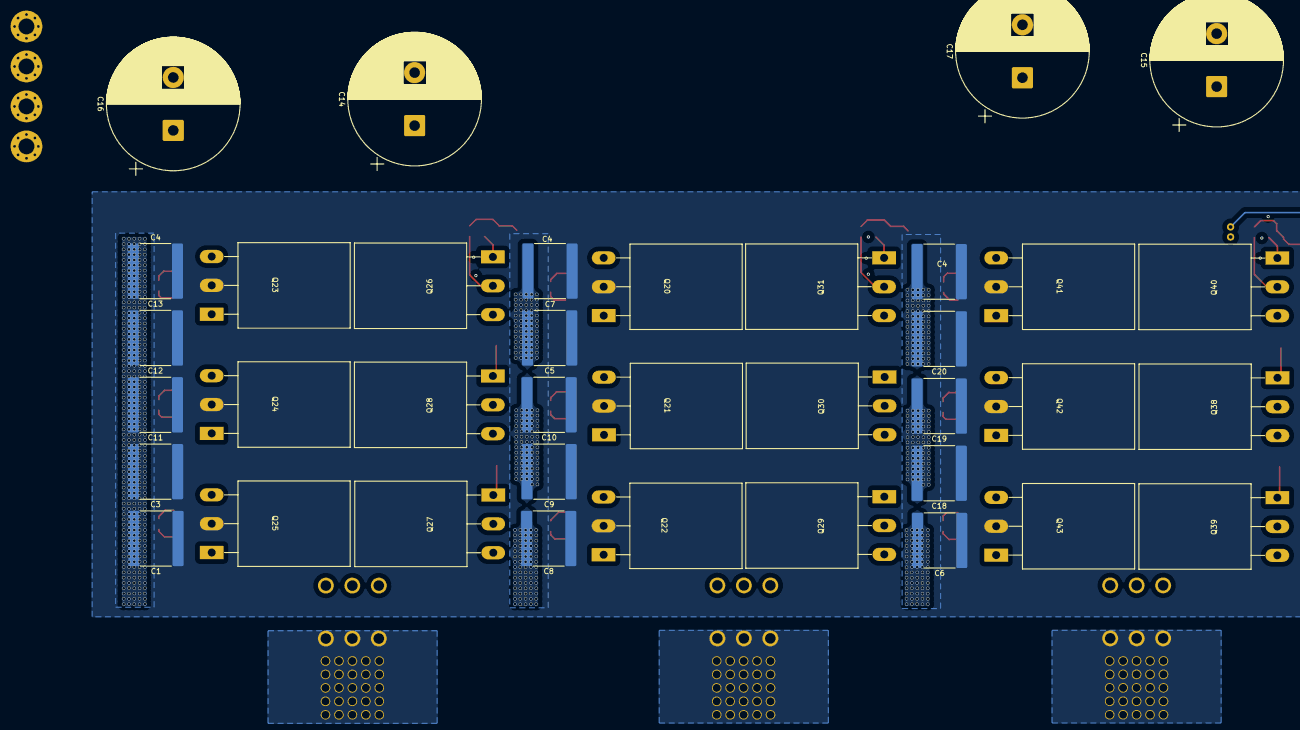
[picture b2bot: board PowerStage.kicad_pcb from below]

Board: 2 copper layers, 102 parts (37 on the bottom side), 30 nets.

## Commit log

2026-06-15 routing pinheader
